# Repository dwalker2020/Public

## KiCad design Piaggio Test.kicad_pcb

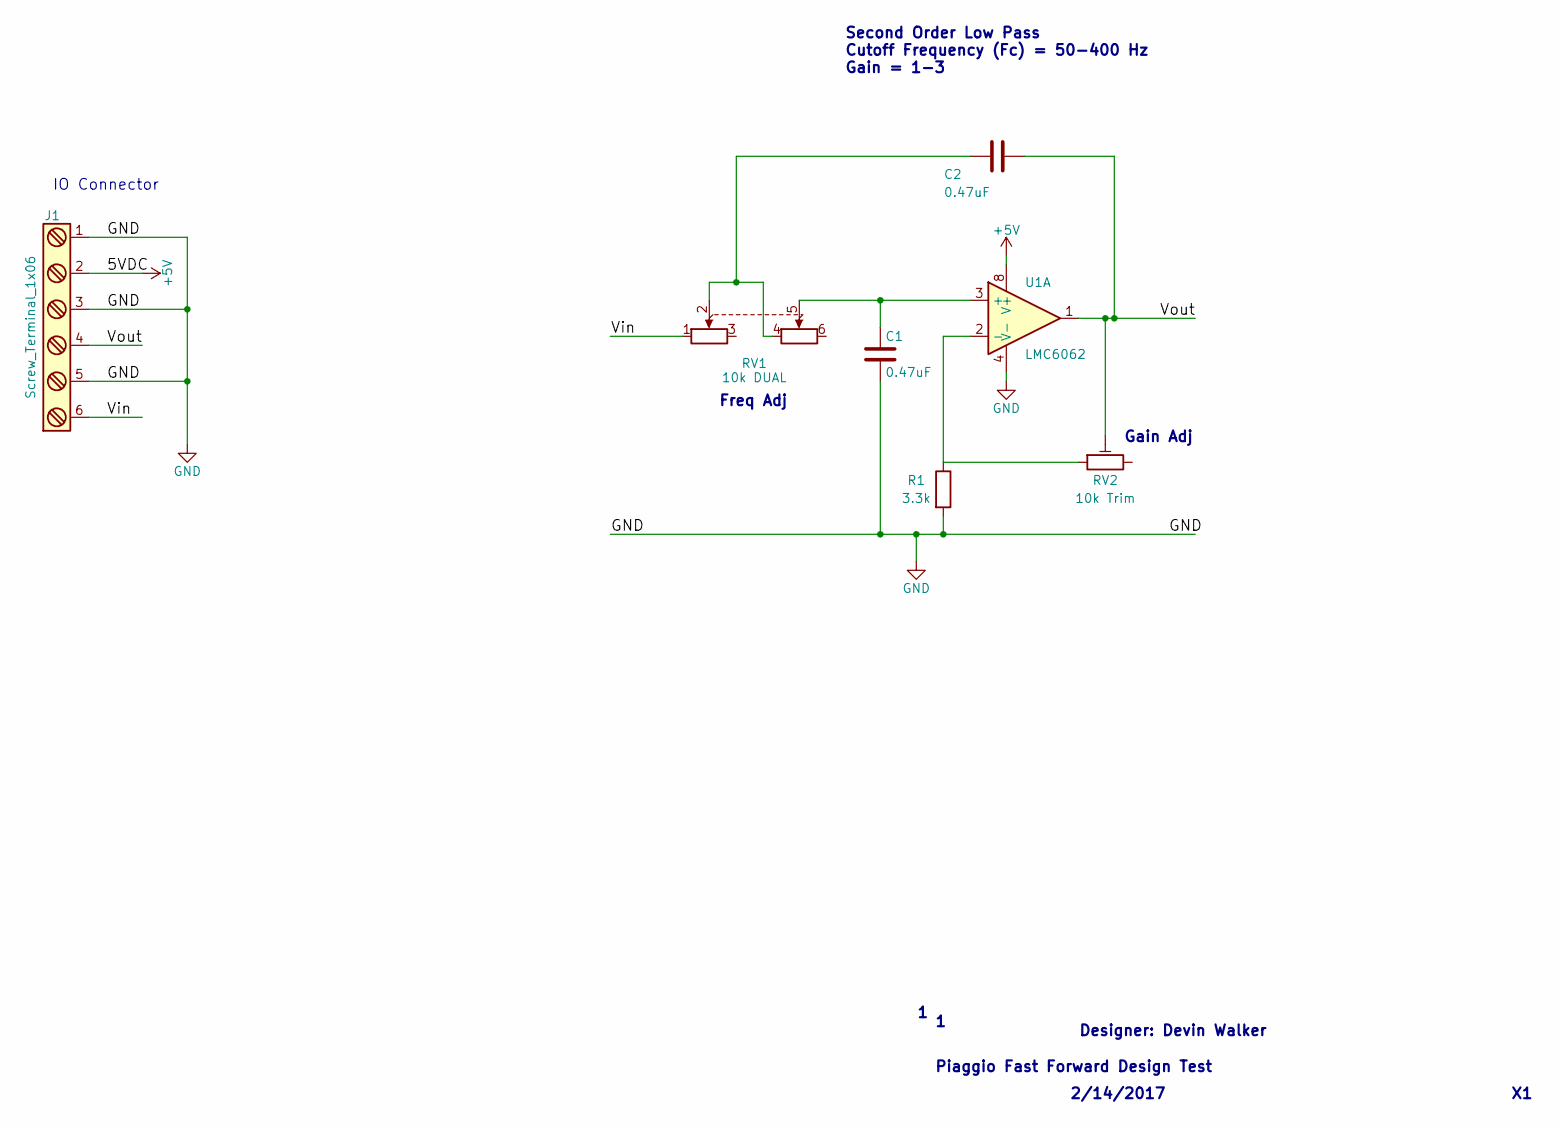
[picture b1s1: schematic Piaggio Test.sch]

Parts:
C1, C2: 0.47uF; C_0603
J1: Screw_Terminal_1x06; TerminalBlock_Pheonix_PT-3.5mm_6pol
R1: 3.3k; R_0402
RV1: 10k DUAL; Potentiometer_Alps_RK097_Double_Vertical
RV2: 10k Trim; Potentiometer_Trimmer_Bourns_3006P
U1: LMC6062; SOIC-8-N

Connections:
+5V: J1.2, U1.8 (V+)
/Vin: J1.6, RV1.1
/Vout: C2.1, J1.4, RV2.2, U1.1
GND: C1.2, J1.1, J1.3, J1.5, R1.2, U1.4 (V-)
unnamed: C1.1, RV1.5, U1.3 (+)
unnamed: C2.2, RV1.2, RV1.4
unnamed: R1.1, RV2.1, U1.2 (-)

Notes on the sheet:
IO Connector
Second Order Low Pass Cutoff Frequency (Fc) = 50-400 Hz Gain = 1-3
Gain Adj
Freq Adj
Piaggio Fast Forward Design Test
2/14/2017
Designer: Devin Walker

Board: 2 copper layers, 7 parts (0 on the bottom side), 7 nets, no tracks yet.

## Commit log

2017-02-14 project
